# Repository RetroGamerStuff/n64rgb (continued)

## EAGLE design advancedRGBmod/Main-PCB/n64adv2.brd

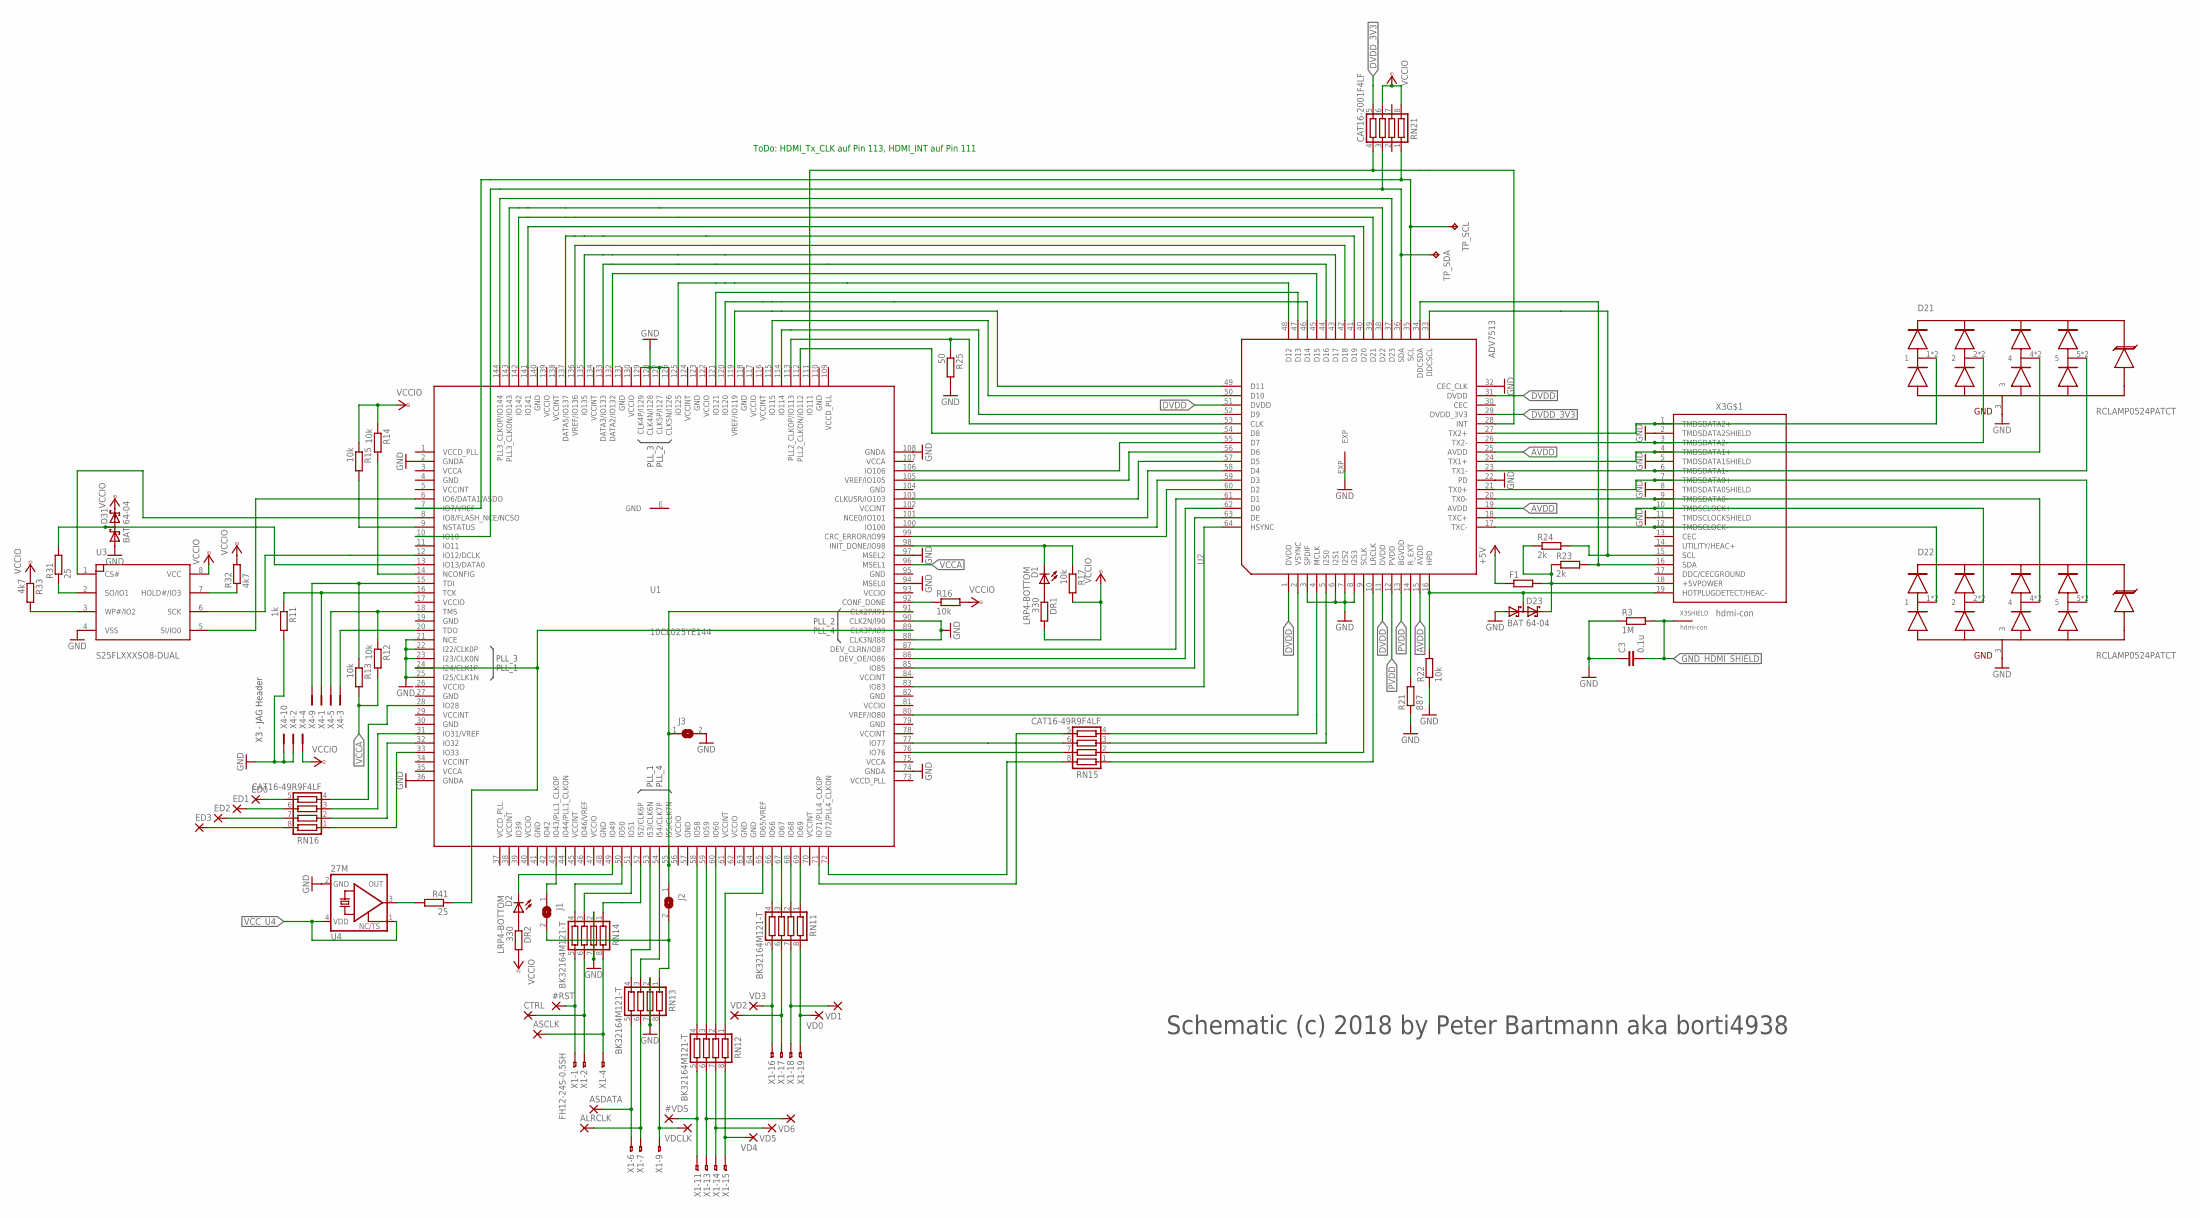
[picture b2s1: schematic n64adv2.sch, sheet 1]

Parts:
#RST: SMD1; SMD0,8-1,6
#VDS: SMD1; SMD0,8-1,6
ALRCLK: SMD1; SMD0,8-1,6
ASCLK: SMD1; SMD0,8-1,6
ASDATA: SMD1; SMD0,8-1,6
C3: 0.1u; C0603
CTRL: SMD1; SMD0,8-1,6
D1, D2: LRP4-BOTTOM; P47F-BOTTOM
D21, D22: RCLAMP0524PATCT; HDMI_RCLAMP
D23, D31: BAT 64-04; SOT23
DR1, DR2: 330; R0603
ED0, ED1, ED2, ED3: SMD1; SMD0,8-1,6
F1: R-EU_R0603; R0603
J1, J2, J3: SJSMALL; SJ_SMALL
R3: 1M; R0603
R11: 1k; R0603
R12, R13, R14, R15, R16, R17, R22: 10k; R0603
R21: 887; R0603
R23, R24: 2k; R0603
R25: 50; R0603
R31, R41: 25; R0603
R32, R33: 4k7; R0603
RN11, RN12, RN13, RN14: BK32164M121-T; CTS742C083
RN15, RN16: CAT16-49R9F4LF; CTS742C083
RN21: CAT16-2001F4LF; CTS742C083
TP_SCL: TPB1,27; B1,27
TP_SDA: TPB1,27; B1,27
U1: 10CL025YE144; EQFP144_2
U2: ADV7513; LQFP64_EP
U3: S25FLXXXSO8-DUAL; SO8-DUAL
U4: 27M; 3.2X2.5_KXO-V96
VD0, VD1, VD2, VD3, VD4, VD5, VD6: SMD1; SMD0,8-1,6
VDCLK: SMD1; SMD0,8-1,6
X1: FH12-24S-0.5SH
X3: hdmi-con; 685119134923
X4: 2510-; PAK100/2500-10

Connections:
+5V: F1.1; also elsewhere on the board
AVDD: U2.15 (AVDD), U2.19 (AVDD), U2.25 (AVDD); also elsewhere on the board
DVDD: U2.1 (DVDD), U2.11 (DVDD), U2.31 (DVDD), U2.51 (DVDD); also elsewhere on the board
DVDD_3V3: RN21.5, U2.29 (DVDD_3V3); also elsewhere on the board
GND: C3.1, D21.3, D22.3, D23.1 (A1), D31.1 (A1), J3.2, R3.1, R11.2, R21.1, R22.1, R25.2, RN13.2, RN13.7, RN14.2, RN14.7, U1.2 (GNDA), U1.4 (GND), U1.19 (GND), U1.21 (NCE), U1.22 (I22/CLK0P), U1.23 (I23/CLK0N), U1.25 (I25/CLK1N), U1.27 (GND), U1.30 (GND), U1.36 (GNDA), U1.41 (GND), U1.48 (GND), U1.57 (GND), U1.63 (GND), U1.64 (GND), U1.74 (GNDA), U1.79 (GND), U1.82 (GND), U1.88 (CLK3N/I88), U1.90 (CLK2N/I90), U1.94 (MSEL0), U1.95 (GND), U1.97 (MSEL2), U1.104 (GND), U1.108 (GNDA), U1.110 (GND), U1.118 (GND), U1.123 (GND), U1.126 (CLK5N/I126), U1.127 (CLK5P/I127), U1.128 (CLK4N/I128), U1.129 (CLK4P/I129), U1.131 (GND), U1.140 (GND), U1.E (GND), U2.3 (SPDIF), U2.6 (I2S1), U2.7 (I2S2), U2.8 (I2S3), U2.22 (PD), U2.32 (CEC_CLK), U2.EXP, U3.4 (VSS), U4.2 (GND), X3.2 (TMDSDATA2SHIELD), X3.5 (TMDSDATA1SHIELD), X3.8 (TMDSDATA0SHIELD), X3.11 (TMDSCLOCKSHIELD), X4.2, X4.10; also elsewhere on the board
GND_HDMI_SHIELD: C3.2, R3.2, X3.SHELL (SHIELD), X3.SHELL1 (SHIELD), X3.SHELL2 (SHIELD), X3.SHELL3 (SHIELD)
unnamed: D1.A, DR1.1
unnamed: RN16.1, U1.33 (IO33)
unnamed: RN16.2, U1.32 (IO32)
unnamed: RN16.3, U1.31 (IO31/VREF)
unnamed: RN16.4, U1.28 (IO28)
unnamed: ED0.P$1, RN16.5
unnamed: ED1.P$1, RN16.6
unnamed: ED2.P$1, RN16.7
unnamed: J1.1, U1.43 (IO43/PLL1_CLKOP)
unnamed: ED3.P$1, RN16.8
unnamed: RN15.5, U1.71 (IO71/PLL4_CLKOP)
unnamed: RN15.6, U1.77 (IO77)
unnamed: D2.C, U1.49 (IO49)
unnamed: J1.2, J2.2, RN13.1
unnamed: U1.85 (IO85), U2.63 (DE)
unnamed: U1.83 (IO83), U2.64 (HSYNC)
unnamed: U1.80 (VREF/IO80), U2.2 (VSYNC)
unnamed: RN15.4, U2.4 (MCLK)
unnamed: RN15.3, U2.5 (I2S0)
unnamed: RN15.2, U2.9 (SCLK)
unnamed: RN15.1, U2.10 (LRCLK)
unnamed: D23.3 (C1A2), R22.2, U2.16 (HPD), X3.19 (HOTPLUGDETECT/HEAC-)
unnamed: D22.1, D22.10 (1), U2.17 (TXC-), X3.12 (TMDSCLOCK-)
unnamed: D22.2, D22.9 (2), U2.18 (TXC+), X3.10 (TMDSCLOCK+)
unnamed: D22.4, D22.7 (4), U2.20 (TX0-), X3.9 (TMDSDATA0-)
unnamed: D22.5, D22.6 (5), U2.21 (TX0+), X3.7 (TMDSDATA0+)
unnamed: D21.5, D21.6 (5), U2.23 (TX1-), X3.6 (TMDSDATA1-)
unnamed: D21.4, D21.7 (4), U2.24 (TX1+), X3.4 (TMDSDATA1+)
unnamed: D21.2, D21.9 (2), U2.26 (TX2-), X3.3 (TMDSDATA2-)
unnamed: D21.1, D21.10 (1), U2.27 (TX2+), X3.1 (TMDSDATA2+)
unnamed: J2.1, J3.1, U1.55 (I55/CLK7N), U1.91 (CLK2P/I91)
unnamed: R24.2, U2.33 (DDCSCL), X3.15 (SCL)
unnamed: R23.2, U2.34 (DDCSDA), X3.16 (SDA)
unnamed: R21.2, U2.14 (R_EXT)
unnamed: RN21.4, U1.111 (IO111), U2.28 (INT)
unnamed: RN11.1, U1.69 (IO69)
unnamed: R31.1, U3.2 (SO/IO1)
unnamed: RN15.7, U1.76 (IO76)
unnamed: R41.2, U4.3 (OUT)
unnamed: D23.2 (C2), F1.2, R23.1, R24.1, X3.18 (+5VPOWER)
unnamed: RN15.8, U1.72 (IO72/PLL4_CLKON)
unnamed: RN11.5, VD3.P$1, X1.16
unnamed: RN11.6, VD2.P$1, X1.17
unnamed: RN11.7, VD1.P$1, X1.18
unnamed: RN11.8, VD0.P$1, X1.19
unnamed: R41.1, U1.24 (I24/CLK1P), U1.89 (CLK3P/I89)
unnamed: D1.C, R17.1, U1.98 (INIT_DONE/IO98)
unnamed: RN11.2, U1.68 (IO68)
unnamed: RN12.1, U1.65 (IO65/VREF)
unnamed: RN12.2, U1.60 (IO60)
unnamed: RN12.3, U1.59 (IO59)
unnamed: RN12.4, U1.58 (IO58)
unnamed: RN12.8, VD4.P$1, X1.15
unnamed: RN12.7, VD5.P$1, X1.14
unnamed: RN12.6, VD6.P$1, X1.13
unnamed: #VDS.P$1, RN12.5, X1.11
unnamed: RN13.8, VDCLK.P$1, X1.9
unnamed: ALRCLK.P$1, RN13.6, X1.7
unnamed: ASDATA.P$1, RN13.5, X1.6
unnamed: RN14.1, U1.52 (I52/CLK6P)
unnamed: RN13.3, U1.54 (I54/CLK7P)
unnamed: RN13.4, U1.53 (I53/CLK6N)
unnamed: ASCLK.P$1, RN14.8, X1.4
unnamed: CTRL.P$1, RN14.6, X1.2
unnamed: #RST.P$1, RN14.5, X1.1
unnamed: RN14.4, U1.50 (IO50)
unnamed: RN14.3, U1.51 (IO51)
unnamed: RN11.3, U1.67 (IO67)
unnamed: U1.8 (IO8/FLASH_NCE/NCSO), U3.1 (CS#)
unnamed: U1.6 (IO6/DATA1/ASDO), U3.5 (SI/IO0)
unnamed: D31.3 (C1A2), R31.2, U1.13 (IO13/DATA0)
unnamed: U1.12 (IO12/DCLK), U3.6 (SCK)
unnamed: R33.2, U3.3 (WP#/IO2)
unnamed: R32.1, U3.7 (HOLD#/IO3)
unnamed: R11.1, U1.16 (TCK), X4.1
unnamed: U1.20 (TDO), X4.3
unnamed: R12.1, U1.18 (TMS), X4.5
unnamed: R13.1, U1.15 (TDI), X4.9
unnamed: RN11.4, U1.66 (IO66)
unnamed: R15.2, U1.9 (NSTATUS)
unnamed: R14.2, U1.14 (NCONFIG)
unnamed: R16.1, U1.92 (CONF_DONE)
unnamed: D2.A, DR2.1
PVDD: U2.12 (PVDD), U2.13 (BGVDD); also elsewhere on the board
SCL: RN21.1, TP_SCL.TP, U1.7 (IO7/VREF), U2.35 (SCL)
SDA: RN21.3, TP_SDA.TP, U1.10 (IO10), U2.36 (SDA)
TX_B0: U1.86 (DEV_OE/IO86), U2.62 (D0)
TX_B1: U1.87 (DEV_CLRN/IO87), U2.61 (D1)
TX_B2: U1.99 (CRC_ERROR/IO99), U2.60 (D2)
TX_B3: U1.100 (IO100), U2.59 (D3)
TX_B4: U1.101 (NCE0/IO101), U2.58 (D4)
TX_B5: U1.103 (CLKUSR/IO103), U2.57 (D5)
TX_B6: U1.105 (VREF/IO105), U2.56 (D6)
TX_B7: U1.106 (IO106), U2.55 (D7)
TX_CLK: R25.1, U1.113 (PLL2_CLKOP/IO113), U2.53 (CLK)
TX_G0: U1.112 (PLL2_CLKON/IO112), U2.54 (D8)
TX_G1: U1.114 (IO114), U2.52 (D9)
TX_G2: U1.115 (IO115), U2.50 (D10)
TX_G3: U1.119 (VREF/IO119), U2.49 (D11)
TX_G4: U1.125 (IO125), U2.48 (D12)
TX_G5: U1.121 (IO121), U2.47 (D13)
TX_G6: U1.120 (IO120), U2.46 (D14)
TX_G7: U1.132 (DATA2/IO132), U2.45 (D15)
TX_R0: U1.133 (DATA3/IO133), U2.44 (D16)
TX_R1: U1.135 (IO135), U2.43 (D17)
TX_R2: U1.136 (VREF/IO136), U2.42 (D18)
TX_R3: U1.137 (DATA5/IO137), U2.41 (D19)
TX_R4: U1.141 (IO141), U2.40 (D20)
TX_R5: U1.142 (IO142), U2.39 (D21)
TX_R6: U1.143 (PLL3_CLKON/IO143), U2.38 (D22)
TX_R7: U1.144 (PLL3_CLKOP/IO144), U2.37 (D23)
VCCA: R12.2, R13.2, U1.3 (VCCA), U1.35 (VCCA), U1.75 (VCCA), U1.96 (MSEL1), U1.107 (VCCA); also elsewhere on the board
VCCD_PLL: U1.1 (VCCD_PLL), U1.37 (VCCD_PLL), U1.73 (VCCD_PLL), U1.109 (VCCD_PLL); also elsewhere on the board
VCCINT: U1.5 (VCCINT), U1.29 (VCCINT), U1.34 (VCCINT), U1.38 (VCCINT), U1.45 (VCCINT), U1.61 (VCCINT), U1.70 (VCCINT), U1.78 (VCCINT), U1.84 (VCCINT), U1.102 (VCCINT), U1.116 (VCCINT), U1.124 (VCCINT), U1.134 (VCCINT), U1.138 (VCCINT); also elsewhere on the board
VCCIO: D31.2 (C2), DR1.2, DR2.2, R14.1, R15.1, R16.2, R17.2, R32.2, R33.1, RN21.6, RN21.8, U1.17 (VCCIO), U1.26 (VCCIO), U1.40 (VCCIO), U1.47 (VCCIO), U1.56 (VCCIO), U1.62 (VCCIO), U1.81 (VCCIO), U1.93 (VCCIO), U1.117 (VCCIO), U1.122 (VCCIO), U1.130 (VCCIO), U1.139 (VCCIO), U3.8 (VCC), X4.4; also elsewhere on the board
VCC_U4: U4.1 (TS), U4.4 (VDD); also elsewhere on the board

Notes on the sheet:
X3 - JAG Header
Schematic (c) 2018 by Peter Bartmann aka borti4938
ToDo: HDMI_Tx_CLK auf Pin 113, HDMI_INT auf Pin 111

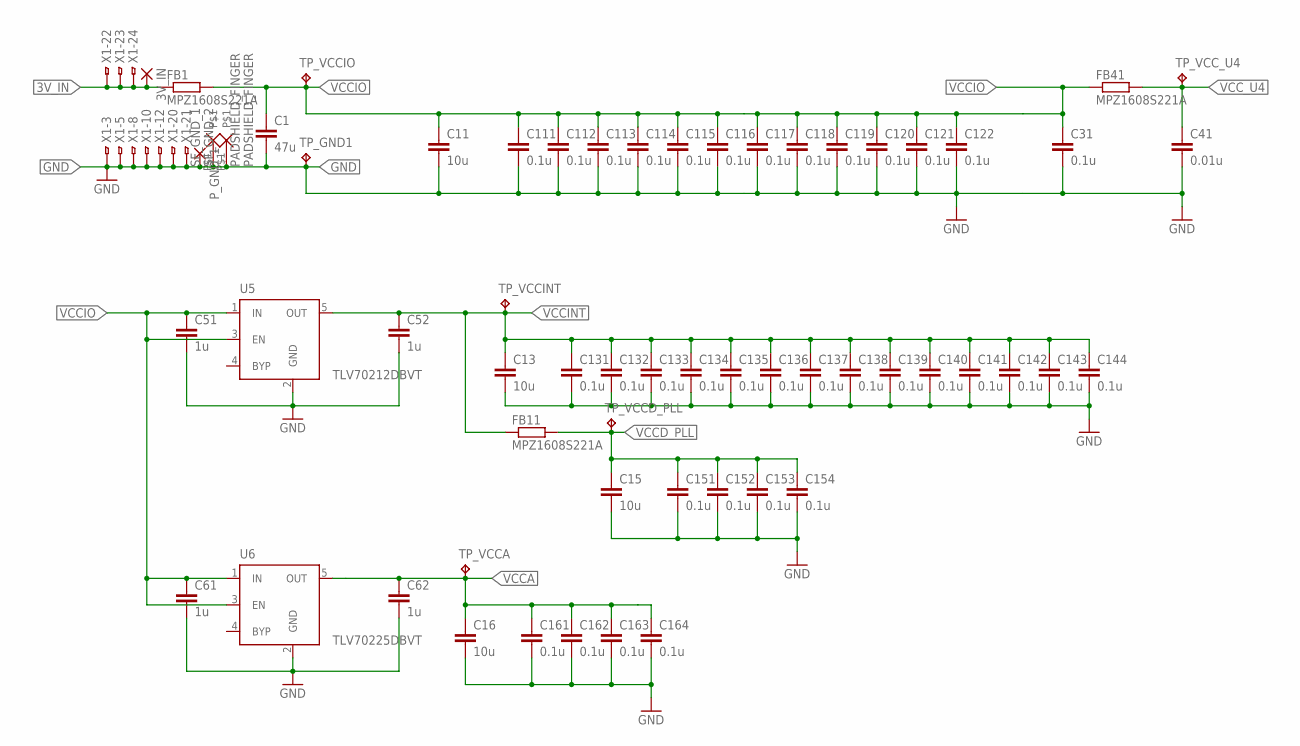
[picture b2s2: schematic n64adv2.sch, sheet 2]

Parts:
3V_IN: SMD2; SMD1,27-2,54
C1: 47u; C0805
C11, C13, C15, C16: 10u; C0805
C31, C111, C112, C113, C114, C115, C116, C117, C118, C119, C120, C121, C122, C131, C132, C133, C134, C135, C136, C137, C138, C139, C140, C141, C142, C143, C144, C151, C152, C153, C154, C161, C162, C163, C164: 0.1u; C0603
C41: 0.01u; C0603
C51, C52, C61, C62: 1u; C0603
FB1, FB11, FB41: MPZ1608S221A; R0603
P_GND_1: SMD2; SMD1,27-2,54
SF_GND_1, SF_GND_2: PADSHIELD_FINGER; GND_FINGER_PAD
TP_GND1: TPB1,27; B1,27
TP_VCCA: TPB1,27; B1,27
TP_VCCD_PLL: TPB1,27; B1,27
TP_VCCINT: TPB1,27; B1,27
TP_VCCIO: TPB1,27; B1,27
TP_VCC_U4: TPB1,27; B1,27
U5: TLV70212DBVT; SOT23-5
U6: TLV70225DBVT; SOT23-5
X1: FH12-24S-0.5SH

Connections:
3V_IN: 3V_IN.1, FB1.1, X1.22, X1.23, X1.24
GND: C1.2, C11.2, C13.2, C15.2, C16.2, C31.2, C41.2, C51.2, C52.2, C61.2, C62.2, C111.2, C112.2, C113.2, C114.2, C115.2, C116.2, C117.2, C118.2, C119.2, C120.2, C121.2, C122.2, C131.2, C132.2, C133.2, C134.2, C135.2, C136.2, C137.2, C138.2, C139.2, C140.2, C141.2, C142.2, C143.2, C144.2, C151.2, C152.2, C153.2, C154.2, C161.2, C162.2, C163.2, C164.2, P_GND_1.1, SF_GND_1.P$1, SF_GND_2.P$1, TP_GND1.TP, U5.2 (GND), U6.2 (GND), X1.3, X1.5, X1.8, X1.10, X1.12, X1.20, X1.21; also elsewhere on the board
VCCA: C16.1, C62.1, C161.1, C162.1, C163.1, C164.1, TP_VCCA.TP, U6.5 (OUT); also elsewhere on the board
VCCD_PLL: C15.1, C151.1, C152.1, C153.1, C154.1, FB11.2, TP_VCCD_PLL.TP; also elsewhere on the board
VCCINT: C13.1, C52.1, C131.1, C132.1, C133.1, C134.1, C135.1, C136.1, C137.1, C138.1, C139.1, C140.1, C141.1, C142.1, C143.1, C144.1, FB11.1, TP_VCCINT.TP, U5.5 (OUT); also elsewhere on the board
VCCIO: C1.1, C11.1, C31.1, C51.1, C61.1, C111.1, C112.1, C113.1, C114.1, C115.1, C116.1, C117.1, C118.1, C119.1, C120.1, C121.1, C122.1, FB1.2, FB41.1, TP_VCCIO.TP, U5.1 (IN), U5.3 (EN), U6.1 (IN), U6.3 (EN); also elsewhere on the board
VCC_U4: C41.1, FB41.2, TP_VCC_U4.TP; also elsewhere on the board

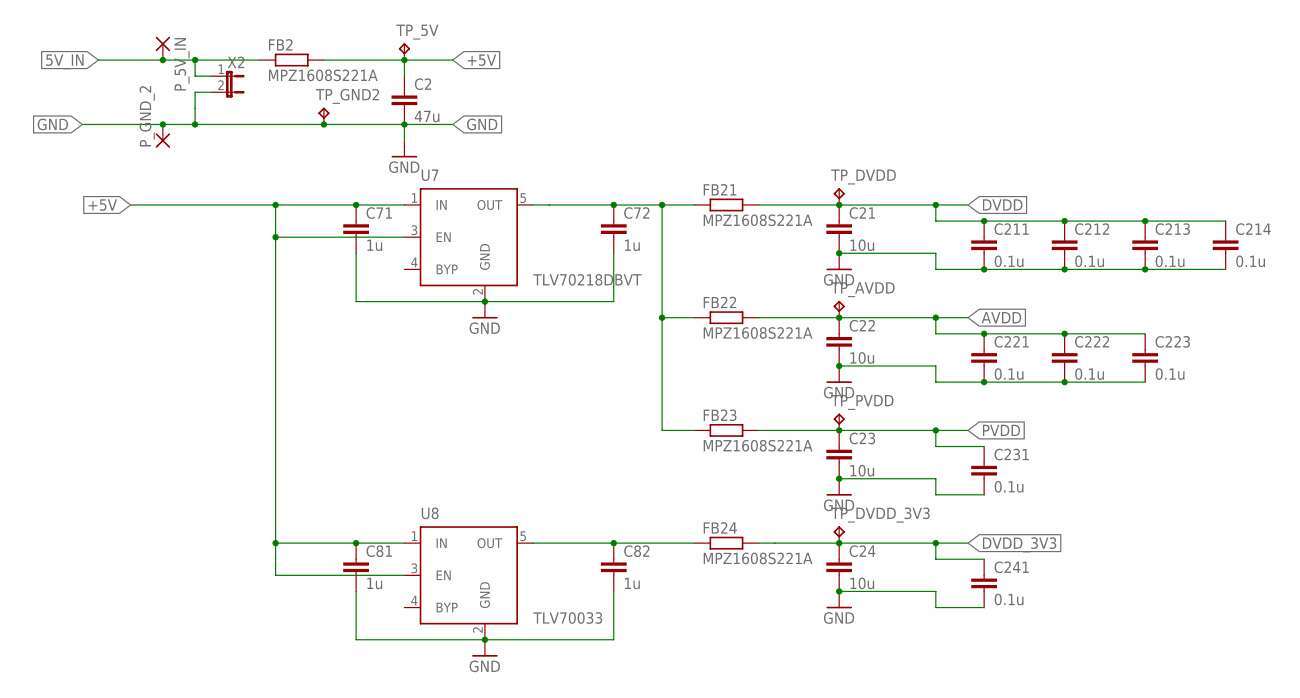
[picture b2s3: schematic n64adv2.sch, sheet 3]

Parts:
C2: 47u; C0805
C21, C22, C23, C24: 10u; C0805
C71, C72, C81, C82: 1u; C0603
C211, C212, C213, C214, C221, C222, C223, C231, C241: 0.1u; C0603
FB2, FB21, FB22, FB23, FB24: MPZ1608S221A; R0603
P_5V_IN: SMD2; SMD1,27-2,54
P_GND_2: SMD2; SMD1,27-2,54
TP_5V: TPB1,27; B1,27
TP_AVDD: TPB1,27; B1,27
TP_DVDD: TPB1,27; B1,27
TP_DVDD_3V3: TPB1,27; B1,27
TP_GND2: TPB1,27; B1,27
TP_PVDD: TPB1,27; B1,27
U7: TLV70218DBVT; SOT23-5
U8: TLV70033; SOT23-5
X2: JP1E; JP1

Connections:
1.8V_PRE: C72.1, FB21.1, FB22.1, FB23.1, U7.5 (OUT)
3.3V_PRE: C82.1, FB24.1, U8.5 (OUT)
5V_IN: FB2.1, P_5V_IN.1, X2.1
+5V: C2.1, C71.1, C81.1, FB2.2, TP_5V.TP, U7.1 (IN), U7.3 (EN), U8.1 (IN), U8.3 (EN); also elsewhere on the board
AVDD: C22.1, C221.1, C222.1, C223.1, FB22.2, TP_AVDD.TP; also elsewhere on the board
DVDD: C21.1, C211.1, C212.1, C213.1, C214.1, FB21.2, TP_DVDD.TP; also elsewhere on the board
DVDD_3V3: C24.1, C241.1, FB24.2, TP_DVDD_3V3.TP; also elsewhere on the board
GND: C2.2, C21.2, C22.2, C23.2, C24.2, C71.2, C72.2, C81.2, C82.2, C211.2, C212.2, C213.2, C214.2, C221.2, C222.2, C223.2, C231.2, C241.2, P_GND_2.1, TP_GND2.TP, U7.2 (GND), U8.2 (GND), X2.2; also elsewhere on the board
PVDD: C23.1, C231.1, FB23.2, TP_PVDD.TP; also elsewhere on the board

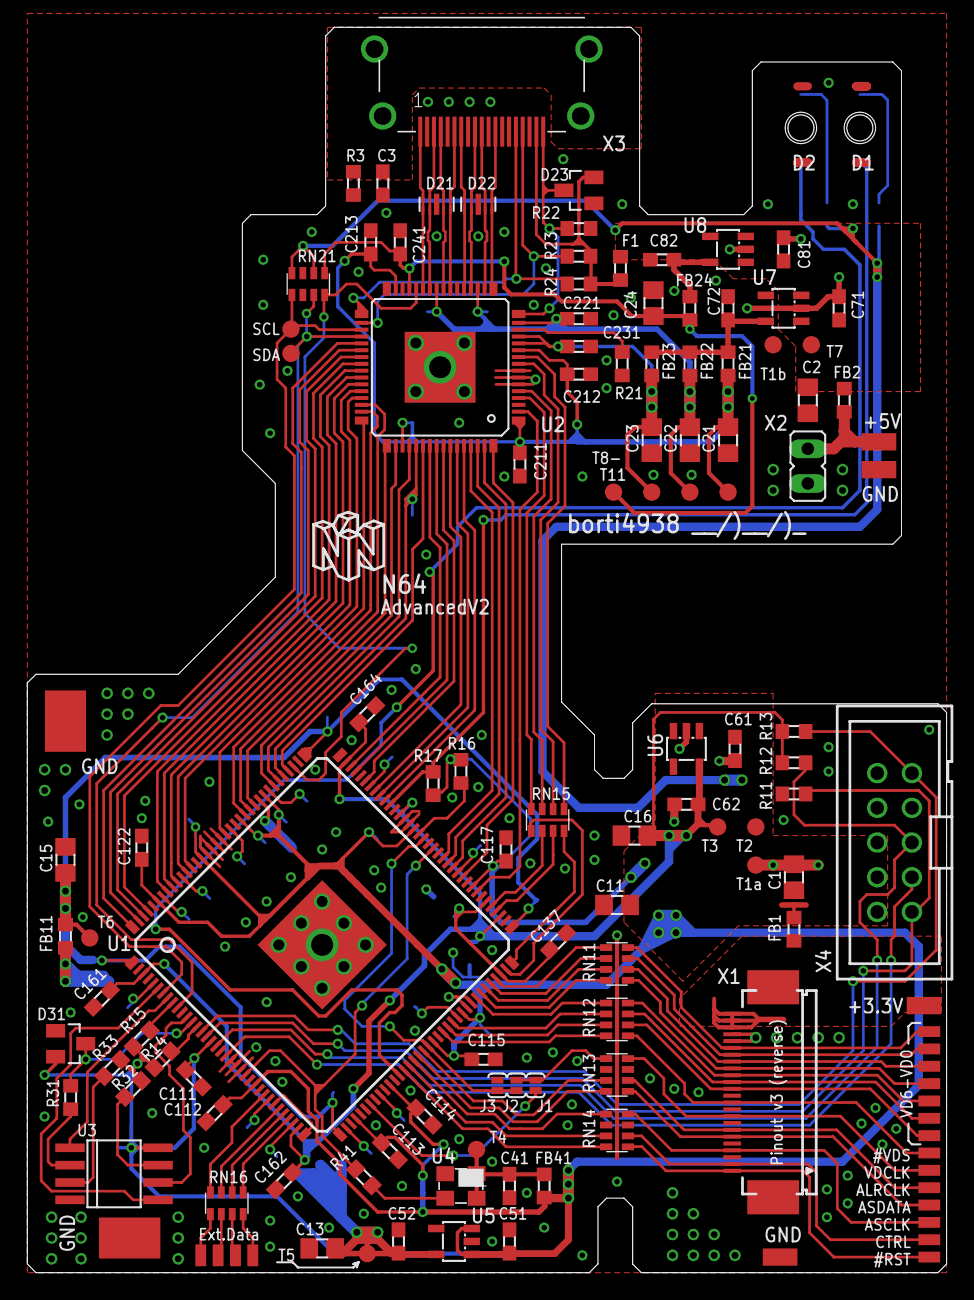
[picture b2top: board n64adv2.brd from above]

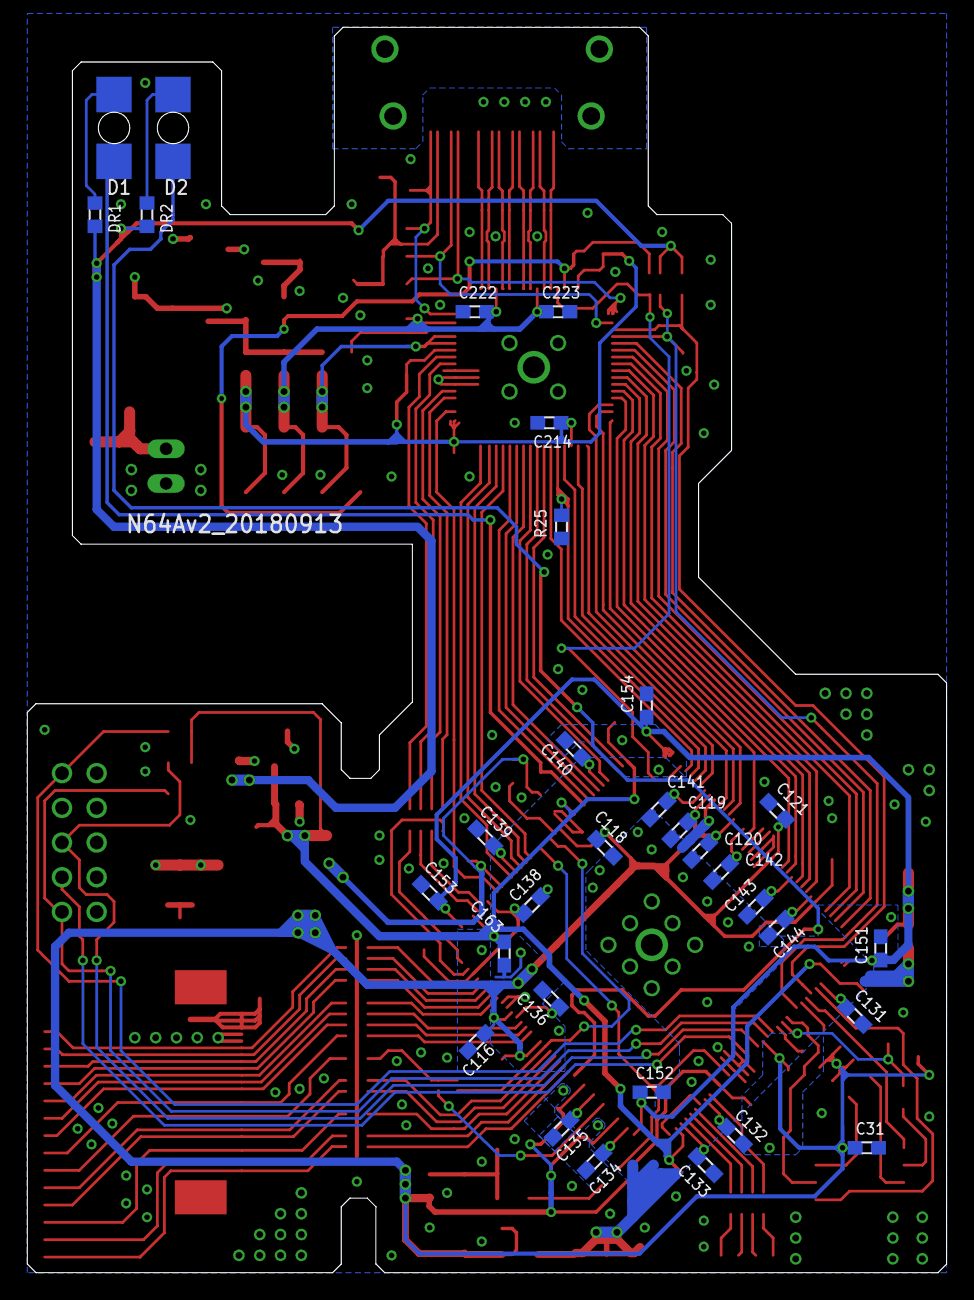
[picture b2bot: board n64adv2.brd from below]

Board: 2 copper layers, 67.3 x 91.2 mm, 158 parts (32 on the bottom side), 126 nets.

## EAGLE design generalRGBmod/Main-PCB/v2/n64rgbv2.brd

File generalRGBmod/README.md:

# General N64 RGB Digital-to-Analog Mod

This folder contains all you need for a complete DIY RGB mod.

Please don't ask me for selling a modding. I either sell some prototypes on some forums marketplaces (which is very unlikely) or I don't have any of the boards.
This is a complete DIY modding project. So everybody is on his own here.
If you are looking for a ready to install kit, just look on your own for a seller. Preferably you should invest your money into a [kit made by viletim](http://etim.net.au/shop/shop.php?crn=209). I also provide similar firmware files for his board in another GitHub repository named [n64rgb_fw4viletim](https://github.com/borti4938/n64rgb_fw4viletim) (note that I do not provide support for the firmware port there).

**WARNING:** This is an advanced DIY project if you do everything on your own. You need decent soldering skills. The CPLD has 0.5mm fine pitch with 100pins. Next to it the video amp has a 0.65mm pin pitch on the board there are some SMD1206 resistor and ferrit bead arrays.

## Features

- Supporting for different CPLDs on a common PCB design:
  * MaxII EPM240T100C5
  * MaxII EPM570T100C5
  * MaxV 5M240ZT100C5
  * MaxV 5M570ZT100C5
- Video DAC:
  * V2: Video DAC ADV7125
- Detection of 240p/288p vs. 480i/576i together with detection of NTSC vs. PAL mode
- optional VI-De-Blur in 240p/288p (horizontal resolution decreased from 640 to 320 pixels)
- optional 16bit color mode
- IGR features:
  * reset the console with the controller (can be disabled via jumper)
  * full control on de-blur and 16bit mode with the controller (can be disabled via jumper)
- optional dedicated mechanical switches for toggling VI-Deblur and 16bit color mode

The following shortly describes the main features of the firmware and how to use / control them.

#### Notes

### In-Game Routines (IGR)

Three functionalities are implemented: toggle de-blur feature and toggle the 16bit mode as well as resetting the console.

The button combination are as follows:

- reset the console: Z + Start + R + A + B
- (de)activate de-blur:
  - deactivate: Z + Start + R + C-le
  - activate: Z + Start + R + C-ri
- (de)activate 16bit mode:
  - deactivate: Z + Start + R + C-up
  - activate: Z + Start + R + C-dw

_Modifiying the IGR Button Combinations_:  
It's difficult to make everybody happy with it. Third party controllers, which differ from the original ones by design, make it even more difficult. So it is possible to generate your own firmware with **your own** preferred **button combinations** implemented. Please refere to the document **IGR.README.md** located in the top folder of this repository for further information.

_Final remark on IGR_:  
However, as the communication between N64 and the controller goes over a single wire, sniffing the input is not an easy task (and probably my solution is not the best one). This together with the lack of an exhaustive testing (many many games out there as well my limited time), I'm looking forward to any incomming issue report to furhter improve this feature :)

### VI-DeBlur

VI-Deblur of the picture information is only be done in 240p/288p. This is be done by simply blanking every second pixel. Normally, the blanked pixels are used to introduce blur by the N64 in 240p/288p mode. However, some games like Mario Tennis, 007 Goldeneye, and some others use these pixel for additional information rather than for blurring effects. In other words this means that these games uses full horizontal resolution even in 240p/288p output mode. Hence, the picture looks more blurry in this case if de-blur feature is activated.

### 16bit Color Mode

The 16bit color mode reduces the color depth from 21bit (7bit for each color) downto 16bits (5bit for red and blue, 6bit for green). Some very few games processes the color information in 16bit. The 16bit color mode simply sets LSBs to '0'.

### Jumpers

There are five jumpers on the modding board - two double solder jumper and three standard jumper.  
For double jumper, jumper Jxx.1 is indicated by an arrow, Jxx.2 is on the opposite side.

- J11.1 -> activates VI-deblur if closed. **[1]**
- J11.2 -> activates 16bit color mode **[1]**
- J12.x -> disables IGR functions if closed
  - x.1: VI-DeBlur and 16bit mode toggle by controller
  - x.2: reset by controller
- J21 -> enables Sync on Green if closed
- J31 -> 75ohm CSync Level
  - open: ~1.87Vpp at a 75ohm termination, i.e. you need an additional resistor in your RGB cables sync line to further attenuate voltage level
  - closed: ~300mVpp at a 75ohm termination, which is standard, i.e. you must not have any components attached to your RGB cables sync line
- J2: toggles video low pass filter of the Filter AddOn
  - open: enabled
  - closed: bypassed 

**Notes**:  

**[1]**  
Jumper becomes active on power cycle or if toggled while running operation.  

## Technical Information

A complete installation and setup guide to this modding kit is provided in the main folder of the repository. Here are some additional short notes.

### Checklist: How to build the project

- Use PCB files to order your own PCB or simply use the shared project on OSHPark
- Source the components you need, e.g. from Mouser
- Wait for everything to arrive
- Assemble your PCB:
  * If you use a MaxII CPLD, you have to assemble FB3 and must not use U4, C41 and C42.
  * If you use a MaxV CPLD, you need U4 (a 1.8V voltage regulator), C41 and C42. Don't touch FB3 in this case!
- Flash the firmware to the CPLD:
  * You need a Altera USB Blaster
  * The board needs to be powered; so you may consider to install the PCB into your N64 first and then use the N64 for powering the board
  * If you want to build an adapter, you may take a look onto [my DIY adapter](https://oshpark.com/shared_projects/mEwjoesz) at [my profile on OSHPark](https://oshpark.com/profiles/borti4938)
- Install the modding board:
  * Installation description is part of the guide located in the top folder.
  * However an installation guide of a similar product made by viletim is provided [here](http://etim.net.au/n64rgb/). Keep in mind that there are minor differences.
  * You have to be aware of the pinout of your video-encoder build into your N64. Pads on the DIY modding board are labeled.

### Source the PCB
Choose the PCB service which suits you. Here are some:

- OSHPark: look onto [my profile](https://oshpark.com/profiles/borti4938)
- PCBWay.com: [Link](http://www.pcbway.com/), [Affiliate Link](http://www.pcbway.com/setinvite.aspx?inviteid=10658)

### BOM / Part List for the PCB
This part list a recommendation how the PCB is designed. If you are able to find pin-compatible devices / parts, you can use them.

The manufacturer's part numbers (MPNs) are just to help you to source appropriate components.

### Firmware
The firmware is located in the folder firmware/. To build the firmware on your own you need Quartus Prime Lite (any version which supports MaxII and MaxV devices).

If you only want to flash the firmware, the configuration files are pre-compiled and located in firmware/output_files. You need the POF appropriate for the CPLD you have choosen (look for the *\_extension*).

For flashing you need:

- Altera USB Blaster
- Standalone Quartus Prime Programmer and Tools

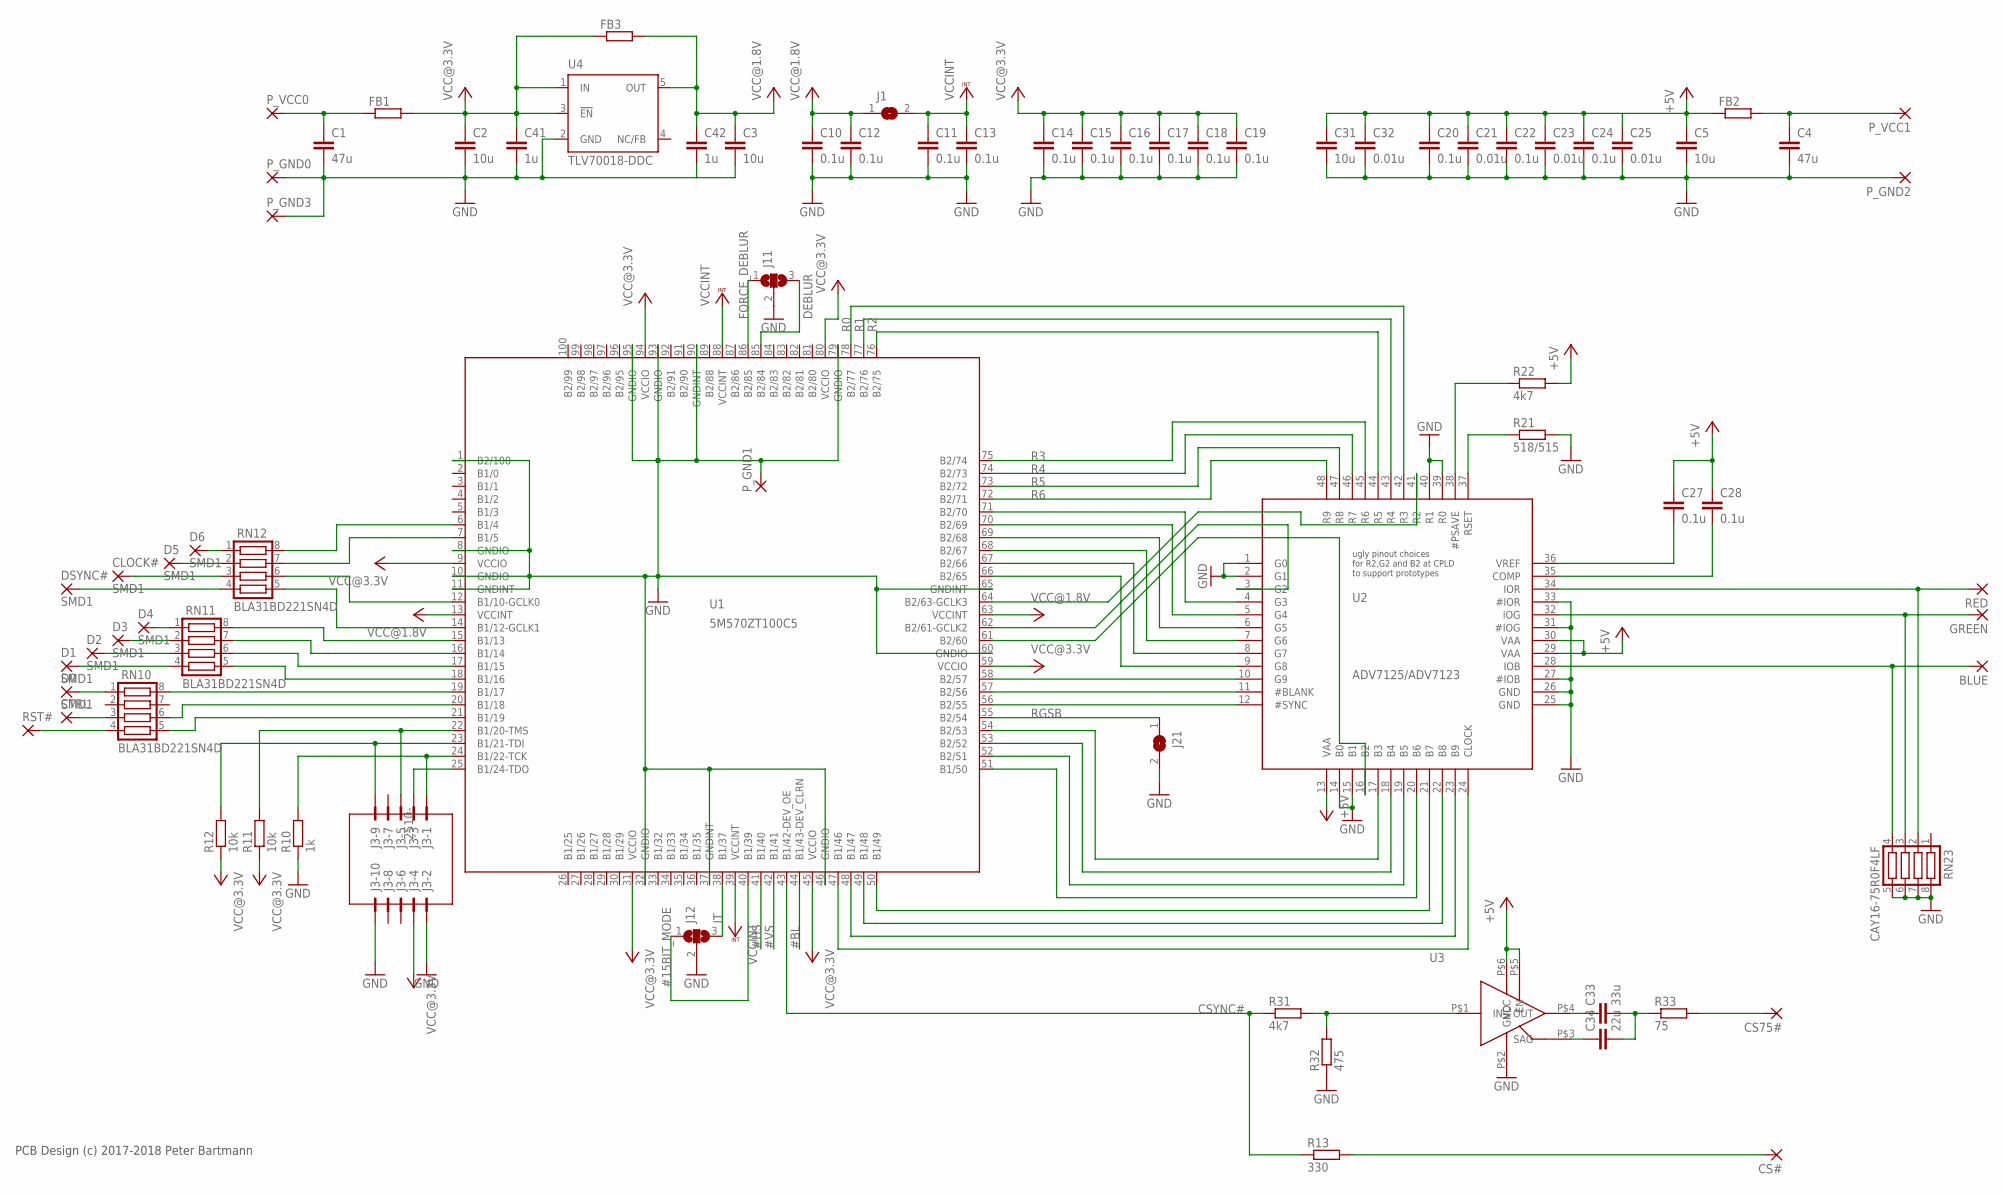
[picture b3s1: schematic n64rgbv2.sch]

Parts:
BLUE: SMD2; SMD1,27-2,54
C1, C4: 47u; C0805
C2, C3, C5, C31: 10u; C0805
C10, C11, C12, C13, C14, C15, C16, C17, C18, C19, C20, C22, C24, C27, C28: 0.1u; C0603
C21, C23, C25, C32: 0.01u; C0603
C33: 33u; C1210
C34: 22u; C1206
C41, C42: 1u; C0603
CLOCK#: SMD1; SMD0,8-1,6
CS75#: SMD2; SMD1,27-2,54
CS#: SMD2; SMD1,27-2,54
CTRL: SMD2; SMD1,27-2,54
D0, D1, D2, D3, D4, D5, D6: SMD1; SMD0,8-1,6
DSYNC#: SMD1; SMD0,8-1,6
FB1, FB2, FB3: R-EU_R0603; R0603
GREEN: SMD2; SMD1,27-2,54
J1, J21: SJ
J3: 2510-; PAK100/2500-10
J11, J12: SJ2W; SJ_2
P_GND0, P_GND1, P_GND2, P_GND3: SMD2; SMD1,27-2,54
P_VCC0, P_VCC1: SMD2; SMD1,27-2,54
R10: 1k; R0603
R11, R12: 10k; R0603
R13: 330; R0603
R21: 518/515; R0603
R22, R31: 4k7; R0603
R32: 475; R0603
R33: 75; R0603
RED: SMD2; SMD1,27-2,54
RN10, RN11, RN12: BLA31BD221SN4D; CTS742C083
RN23: CAY16-75R0F4LF; CTS742C083
RST#: SMD2; SMD1,27-2,54
U1: 5M570ZT100C5; TQFP100
U2: ADV7125/ADV7123; LQFP48
U3: TSH122ICT; SC70
U4: TLV70018-DDC; SOT23-DBV

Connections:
#15BIT_MODE: J12.1, U1.40 (B1/39)
#BL: U1.44 (B1/43-DEV_CLRN)
#HS: U1.41 (B1/40)
#VS: U1.42 (B1/41)
+5V: C5.1, C20.1, C21.1, C22.1, C23.1, C24.1, C25.1, C27.1, C28.1, C31.1, C32.1, FB2.1, R22.2, U2.13 (VAA), U2.29 (VAA), U2.30 (VAA), U3.P$5 (EN), U3.P$6 (VCC)
BLUE: BLUE.1, RN23.4, U2.28 (IOB)
CSYNC#: R13.1, R31.1, U1.43 (B1/42-DEV_OE)
DEBLUR: J11.3, U1.85 (B2/84)
FORCE_DEBLUR: J11.1, U1.86 (B2/85)
GND: C1.2, C2.2, C3.2, C4.2, C5.2, C10.2, C11.2, C12.2, C13.2, C14.2, C15.2, C16.2, C17.2, C18.2, C19.2, C20.2, C21.2, C22.2, C23.2, C24.2, C25.2, C31.2, C32.2, C41.2, C42.2, J3.2, J3.10, J11.2, J12.2, J21.2, P_GND0.1, P_GND1.1, P_GND2.1, P_GND3.1, R10.1, R21.2, R32.1, RN23.5, RN23.6, RN23.7, RN23.8, U1.1 (B2/100), U1.8 (GNDIO), U1.10 (GNDIO), U1.11 (GNDINT), U1.32 (GNDIO), U1.37 (GNDINT), U1.46 (GNDIO), U1.60 (GNDIO), U1.65 (GNDINT), U1.79 (GNDIO), U1.90 (GNDINT), U1.93 (GNDIO), U1.95 (GNDIO), U2.1 (G0), U2.2 (G1), U2.14 (B0), U2.15 (B1), U2.25 (GND), U2.26 (GND), U2.27 (#IOB), U2.31 (#IOG), U2.33 (#IOR), U2.39 (R0), U2.40 (R1), U3.P$2 (GND), U4.2 (GND)
GREEN: GREEN.1, RN23.3, U2.32 (IOG)
IT: J12.3, U1.38 (B1/37)
unnamed: D6.P$1, RN12.1
unnamed: D5.P$1, RN12.2
unnamed: DSYNC#.P$1, RN12.4
unnamed: CLOCK#.P$1, RN12.3
unnamed: RN10.4, RST#.1
unnamed: CTRL.1, RN10.3
unnamed: D0.P$1, RN10.1
unnamed: RN10.8, U1.19 (B1/17)
unnamed: RN10.6, U1.20 (B1/18)
unnamed: RN10.5, U1.21 (B1/19)
unnamed: RN11.5, U1.18 (B1/16)
unnamed: RN11.6, U1.17 (B1/15)
unnamed: CS#.1, R13.2
unnamed: RN11.7, U1.16 (B1/14)
unnamed: RN11.8, U1.15 (B1/13)
unnamed: D1.P$1, RN11.4
unnamed: D2.P$1, RN11.3
unnamed: D3.P$1, RN11.2
unnamed: D4.P$1, RN11.1
unnamed: RN12.7, U1.7 (B1/5)
unnamed: RN12.8, U1.6 (B1/4)
unnamed: RN12.5, U1.14 (B1/12-GCLK1)
unnamed: RN12.6, U1.12 (B1/10-GCLK0)
unnamed: U1.71 (B2/70), U2.4 (G3)
unnamed: U1.64 (B2/63-GCLK3), U2.41 (R2)
unnamed: U1.70 (B2/69), U2.5 (G4)
unnamed: U1.69 (B2/68), U2.6 (G5)
unnamed: U1.68 (B2/67), U2.7 (G6)
unnamed: U1.67 (B2/66), U2.8 (G7)
unnamed: U1.66 (B2/65), U2.9 (G8)
unnamed: U1.58 (B2/57), U2.10 (G9)
unnamed: U1.56 (B2/55), U2.12 (#SYNC)
unnamed: U1.47 (B1/46), U2.24 (CLOCK)
unnamed: U1.48 (B1/47), U2.23 (B9)
unnamed: U1.49 (B1/48), U2.22 (B8)
unnamed: U1.50 (B1/49), U2.21 (B7)
unnamed: U1.51 (B1/50), U2.20 (B6)
unnamed: U1.52 (B2/51), U2.19 (B5)
unnamed: U1.53 (B2/52), U2.18 (B4)
unnamed: U1.54 (B2/53), U2.17 (B3)
unnamed: U1.62 (B2/61-GCLK2), U2.3 (G2)
unnamed: U1.57 (B2/56), U2.11 (#BLANK)
unnamed: U1.61 (B2/60), U2.16 (B2)
unnamed: C4.1, FB2.2, P_VCC1.1
unnamed: C1.1, FB1.1, P_VCC0.1
unnamed: C33.2, C34.2, R33.1
unnamed: CS75#.1, R33.2
unnamed: C33.1, U3.P$4 (OUT)
unnamed: C34.1, U3.P$3 (SAG)
unnamed: R21.1, U2.37 (RSET)
unnamed: R22.1, U2.38 (#PSAVE)
unnamed: C28.2, U2.35 (COMP)
unnamed: R31.2, R32.2, U3.P$1 (IN)
unnamed: C27.2, U2.36 (VREF)
R0: U1.78 (B2/77), U2.42 (R3)
R1: U1.77 (B2/76), U2.43 (R4)
R2: U1.76 (B2/75), U2.44 (R5)
R3: U1.75 (B2/74), U2.45 (R6)
R4: U1.74 (B2/73), U2.46 (R7)
R5: U1.73 (B2/72), U2.47 (R8)
R6: U1.72 (B2/71), U2.48 (R9)
RED: RED.1, RN23.2, U2.34 (IOR)
RGSB: J21.1, U1.55 (B2/54)
TCK: J3.1, R10.2, U1.24 (B1/22-TCK)
TDI: J3.9, R12.2, U1.23 (B1/21-TDI)
TDO: J3.3, U1.25 (B1/24-TDO)
TMS: J3.5, R11.2, U1.22 (B1/20-TMS)
VCC@1.8V: C3.1, C10.1, C12.1, C42.1, FB3.2, J1.1, U1.13 (VCCINT), U1.63 (VCCINT), U4.5 (OUT)
VCC@3.3V: C2.1, C14.1, C15.1, C16.1, C17.1, C18.1, C19.1, C41.1, FB1.2, FB3.1, J3.4, R11.1, R12.1, U1.9 (VCCIO), U1.31 (VCCIO), U1.45 (VCCIO), U1.59 (VCCIO), U1.80 (VCCIO), U1.94 (VCCIO), U4.1 (IN), U4.3 (!EN)
VCCINT: C11.1, C13.1, J1.2, U1.39 (VCCINT), U1.88 (VCCINT)

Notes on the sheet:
ugly pinout choices for R2,G2 and B2 at CPLD to support prototypes
PCB Design (c) 2017-2018 Peter Bartmann
